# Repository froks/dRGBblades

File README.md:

dRGBblades
==========

dRGBblades is a small pcb to drive a lpd8806-based led stripe on a rc-helicopter blade with a 1s lipo

It consists of a DC/DC-converter that converts the 1s lipo input voltage (3.3-4.2V) to a 5V/2A output
to power the led stripe and a atmel attiny84 to control the digital side of the stripe.

The DC/DC-converter is based on a LT3436 (http://cds.linear.com/docs/en/datasheet/3436fa.pdf) switching
regulator.

dRGBblades on a voodoo 600 installed on radix 600mm blades:

dRGBblades stripe only test video:

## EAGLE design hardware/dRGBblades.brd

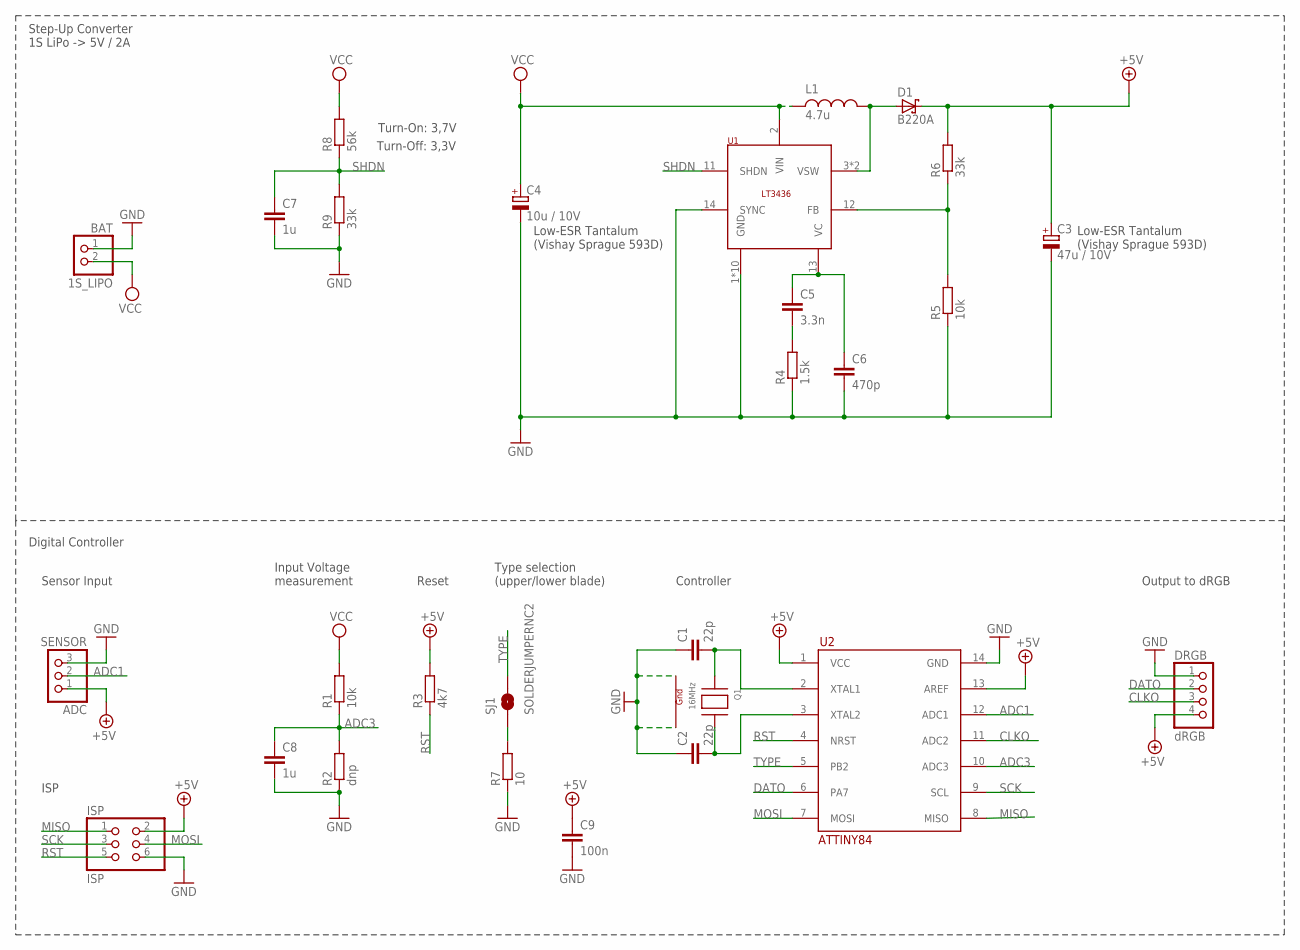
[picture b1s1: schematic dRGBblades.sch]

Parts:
ADC: SENSOR; 1X03/90
BAT: 1S_LIPO; 1X02/90
C1, C2: 22p; C0603
C3: 47u / 10V; D/7343-31W
C4: 10u / 10V; A/3216-18W
C5: 3.3n; C0603
C6: 470p; C0603
C7, C8: 1u; C0603
C9: 100n; C0603
D1: B220A; SMA
DRGB: dRGB; 1X04/90
ISP: ISP; 2X03/90
L1: 4.7u; INDUCTOR-SUMIDA-CDRH6
Q1: 16MHz; NX3225
R1, R5: 10k; R0603
R2: dnp; R0603
R3: 4k7; R0603
R4: 1.5k; R0603
R6, R9: 33k; R0603
R7: 10; R0603
R8: 56k; R0603
SJ1: SOLDERJUMPERNC2; SJ_2S-NOTRACE
U1: LT3436; TSSOP-17
U2: ATTINY84; SO14

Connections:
+5V: ADC.1, C3.+, C9.1, D1.C, DRGB.4, ISP.2, R3.2, R6.2, U2.1 (VCC), U2.13 (AREF)
ADC1: ADC.2, U2.12 (ADC1)
ADC3: C8.1, R1.1, R2.2, U2.10 (ADC3)
CLKO: DRGB.3, U2.11 (ADC2)
DATO: DRGB.2, U2.6 (PA7)
GND: ADC.3, BAT.1, C1.1, C2.1, C3.-, C4.-, C6.2, C7.2, C8.2, C9.2, DRGB.1, ISP.6, Q1.2 (G2), Q1.4 (G1), R2.1, R4.1, R5.1, R7.1, R9.1, U1.1 (GND), U1.5 (GND), U1.6 (GND), U1.7 (GND), U1.8 (GND), U1.9 (GND), U1.10 (GND), U1.14 (SYNC), U1.15 (GND), U1.16 (GND), U1.17 (GND), U2.14 (GND)
MISO: ISP.1, U2.8 (MISO)
MOSI: ISP.4, U2.7 (MOSI)
unnamed: C5.1, C6.1, U1.13 (VC)
unnamed: C2.2, Q1.3 (X2), U2.3 (XTAL2)
unnamed: C1.2, Q1.1 (X1), U2.2 (XTAL1)
unnamed: C5.2, R4.2
unnamed: D1.A, L1.P$2, U1.3 (VSW), U1.4 (VSW)
unnamed: R5.2, R6.1, U1.12 (FB)
unnamed: R7.2, SJ1.1
RST: ISP.5, R3.1, U2.4 (NRST)
SCK: ISP.3, U2.9 (SCL)
SHDN: C7.1, R8.1, R9.2, U1.11 (SHDN)
TYPE: SJ1.2, U2.5 (PB2)
VCC: BAT.2, C4.+, L1.P$1, R1.2, R8.2, U1.2 (VIN)

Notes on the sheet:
Low-ESR Tantalum (Vishay Sprague 593D)
Digital Controller
Sensor Input
ISP
Input Voltage measurement
Reset
Type selection (upper/lower blade)
Controller
Output to dRGB
Turn-On: 3,7V
Turn-Off: 3,3V
Step-Up Converter 1S LiPo -> 5V / 2A

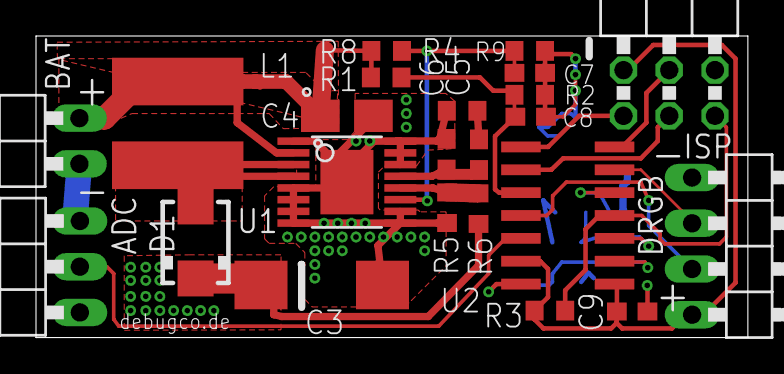
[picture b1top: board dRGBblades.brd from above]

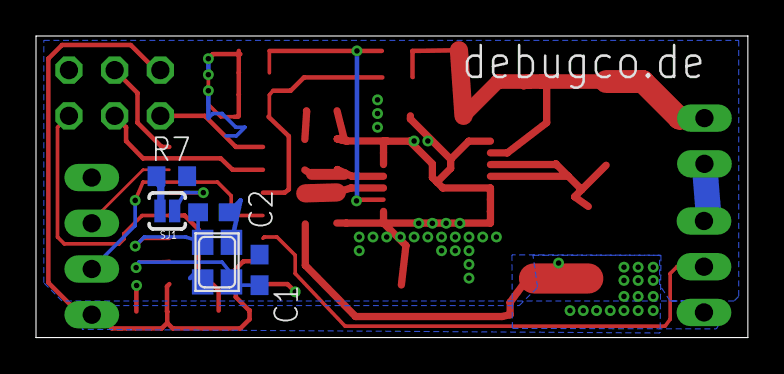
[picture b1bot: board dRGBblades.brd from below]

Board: 2 copper layers, 39.5 x 16.8 mm, 28 parts (5 on the bottom side), 20 nets.

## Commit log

2014-02-05 hardware files initial commit
2014-02-05 software files initial commit
2014-02-05 informative readme
2014-02-07 massive size optimization some bugfixes
2014-02-07 added a ~1sec timer and second counter
2014-02-15 - avr studio 6 - moved some stuff around for more comfortable programming/effect writing
2014-02-17 undervoltage detection finally works
2014-02-17 more effects, cleanup
2014-02-19 more effects
2014-02-20 another effect (experimental)
2014-02-23 more effects / more customization
2014-02-24 new experimental pov effect
2014-03-02 new effect selection
2014-03-02 readme videos
2014-03-02 pictures
2014-03-02 typo
2014-03-04 cleanup effects experimental alphablend between effects

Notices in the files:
parts and their libraries:
SparkFun: Licensing: CC v3.0 Share-Alike You are welcome to use this library for commercial purposes.
